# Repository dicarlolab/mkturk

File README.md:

# [mkturk](mkturk.com)
A purely web-based psychophysics tool for neuroscience and psychology

## Acknowledgement
We are happy to share the mkturk software and hardware and hope it helps with your project. Should this repository help in a substantitive way toward a publication, we would appreciate a brief acknowledgement: "Issa Lab for sharing their web based behavior system (mkturk)."

## Getting started
For getting the web app up and running, see https://mkturk.com/installation.html
Then see the [general guide](https://mkturk.com/features.html) & [detailed guide](https://paper.dropbox.com/doc/MkTurk-Guide--BF6Zcm6igbE2cwsKtibyddKOAg-Vpip4yINDsGnF3JwvBcJT)
[Full list of task parameter definitions](https://github.com/issalab/mkturk/tree/master/public/mkturk)

## Hosting the web app
Running mkturk is as simple as loading a web page since mkturk is purely a client-side piece of code. This requires a server capable of loading an html. Dropbox and Google Drive have stopped serving html, so other options have to be considered such as GitHub, GitLab, Google Firebase or Amazon S3.

### Local hosting of the web app
Even before publishing to the world wide web, mkturk can be run on a local host which is useful for development, debugging, and demo purposes.

### Configuring mkturk_installsettings.js
Compared to a regular app, a web app technically doesn't need to be installed in the traditional sense of the word. However, there are still some deployment-specific options to configure, and these are all found in mkturk_installsettings.js.

## Browser Compatibility
Although as a web app, mkturk should run on any browser on any device, in reality, we rely on Google Chrome which implements the latest APIs such as the WebUSB API. MkTurk will also run on Safari and Firefox browsers if not using an Arduino (which would require Chrome's WebUSB API).

## Setting up the touchscreen device
Depending on the device and which version of Android, you may have control over various settings and will want to adjust the Settings such as touch sensitivity, screen brightness, hiding home menus, disabling side or top swipe menus, disabling automatic dimming of screen, etc.

A very important feature to add is a way to keep the screen on so that it doesn't shut off in the middle of the task. Rather than use an app, we found that by enabling Developer Options, we unlock a feature to keep the screen on. On the latest Android, navigate to Settings -> System -> Developer Options, and enable "Stay awake - Screen will never sleep while charging." Alternatively, you can download an app such as [Keep Screen On](https://play.google.com/store/apps/details?id=eu.aboutall.android.tools.kepscreenon&hl=en). Unfortunately, besides Developer Mode or an app, there is no setting in native Android to prevent the screen from shutting off.

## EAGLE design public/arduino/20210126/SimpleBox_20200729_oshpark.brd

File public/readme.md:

# Parameters

## TASK
Automator: Boolean on/off

AutomatorFilePath: File path to params for the automator curriculum.

BackgroundColor2D: specify the background color in hex (eg, #FFFFFF for white or #000000 for black). Not required in param file. If not provided, defaults to gray screen background (#7F7F7F)

CheckRFID: Time in milliseconds over which at least one matching RFID read is required so that agent doesn't get kicked off of task. If there is a read within the last CheckRFID ms, task continues, otherwise agent is locked out at start of next trial. CheckRFID <= 0 turns off RFID checking.

ChoiceGridIndex: For a same-different task, need to specify two locations, one for same choice (circle) and one for different choice (square).

ChoiceScale (computed internally and stored in ENV.ChoiceScale instead of provided by user in TASK): Size of choice circle and square in units of sample image width

ChoiceSizeInches: Size of choice circle and square in physical inches on the screen

ChoiceTimeOut: Time in milliseconds that subject has to make a choice in AFC task before trial aborts and new sample is displayed. This timeout applies to test response screen in SR2 or M2S and to choice response screen in same-different

ConsecutiveHitsITI: Maximum time in milliseconds allowed to elapse from the previous trial for the current trial to count toward reward accumulation for a string of correct responses. For example, if ConsecutiveHitsITI=8000, then subject has 8 seconds to complete the next trial successfully and the consecutivehits counter will be incremented. Otherwise, the number of consecutivehits will get set to 0

CurrentAutomatorStage: index of current training stage of automator.

FixationDuration: How long subject has to hold fixation touch in milliseconds for a successful fixation to register.

FixationMove: FixationMove=0, fixation image is presented at fixationGridindex. FixationMove=N, N>0, fixation image is presented at a randomly selected grid point and the fixation position is redrawn every N milliseconds. FixationMove > 0 can be used to train subjects to touch different screen locations or to calibrate an eyetracker.
FixationScale: Size of fixation image in units of sample image width.

FixationScale (computed internally and stored in ENV.FixationScale instead of provided by user in TASK params): Size of the fixation dot or image (ie FixationUsesSample=1) in units of sample image width

FixationSizeInches: Size of fixation dot or image (ie FixationUsesSample=1) in physical inches on the screen

FixationTimeOut: Time in milliseconds that subject has to acquire fixation before fixation dot or image extinguishes. If fixation times out, then it is just re-displayed (flashes) and no reward or punishment is administered (ie, trial is aborted)

FixationUsesSample: FixationUsesSample=0, a fixation circle is shown for subject to touch; FixationUsesSample=1, sample image is shown as the fixation image. This allows implementation of a trianing strategy where the subject has to engage the sample image nfixations number of times before the choice screen.

GridScale (deprecated, replaced by GridSpacingInches): Determines intergridpoint spacing. Can think of this as the resolution of grid. gridscale=1 means intergridpoint spacing is equal to the width of the sample image. Finer grid resolutions (gridscale<1) can be used for more precise sample positioning.

GridSpacingInches: Determines intergridpoint spacing in physical inches on screen.

HideChoiceDistractors: HideChoiceDistractors=1, hides the same or different button so that subject sees only the correct one to touch. Still gets punished if touches blank area where the incorrect button would have been. This only applies to same-different choice screen. See HideTestDistractors for test response screen used in SR2 and M2S.

HideTestDistractors: HideTestDistractors=1, hides the distractor choices so that subject only sees matching choice. Still gets punished if touches blank area where the incorrect button would have been.

Homecage: Where task was performed. 0=lab 1=subject's home

ImageBagsSample: List of (list of) paths, where entries at the top level are directories / imagepaths for the sample images of one group; e.g. [['/bear_images', '/dog_images'], '/face_images'] is a {bear, dog} versus face task

ImageBagsTest: List of (list of) paths, where entries at the top level are directories / imagepaths for the test images of one group; e.g. [['/buttons/bear_icon.png, '/buttons/dog_icon.png'], ['/buttons/face_icon1.png, '/buttons/face_icon2.png']]

ImageRewardsList: List of paths containing user-specified reward per image. Images in the image_reward_list file need to be referenced by their complete path. ImageReward values: 0=no feedback (no reward or punish for that sample image) >0=user set reward for that sample image, overrides bonus reward behavior. These can be partial lists. For images where reward is manually specified, then default bonus reward behavior is used. No corresponding list is used for test (choice) images. Instead, specify reward for a whole class by listing reward for each image in that class in ImageRewardsList.

InterTrialInterval: How long to wait after reward/punish is delivered before starting next trial. Only a gray screen is shown for InterTrialInterval milliseconds, followed by the fixation dot.

KeepSampleON: KeepSampleON=0, sample is presented only for sampleON milliseconds for a delayed match-to-sample, KeepSampleON=1 sample remains on during choice screen. This implements a spatial match to sample.

KeepTestON: KeepTestON=0, test is presented only for testON milliseconds, KeepTestON=1 test remains on during choice screen. This only applies to same-different task when responses are indicated on additional choice screen following test screen.

Liquid: 1=water 2=water-condensed milk 3=marshmallow slurry (4/30mL)

NConsecutiveHitsforBonus: How many consecutive hits subject needs for the reward amount to increase.  If NConsecutiveHitsforBonus=4, then subject will get 2x reward for correct responses on 4 consecutive trials, 3x reward for correct responses on 8 consecutive trials, up to nrewardmax times of 1x reward. This is a way to make chance on a 2AFC task be virtually < 50% since reward is jointly distributed across trials rather than independently on the current trial.

NFixations: Number of times fixation dot needs to be pressed to advance to the match to sample phase of the task. nfixations=1 means the subject simply has to press the fixation dot once before the sample is presented. This mode allow parametric control over fixed ratio scheduling.

NGridPoints: Number of display grid points in either direction. Produces square grid. 3x3 is typical. Images (fixation,sample, & test) will appear centered on one of the grid points. Grid is serially zero indexed by rows then columns. ngridpoints can be made larger to allow for more response choices to be simultaneously displayed.

NRewardMax: Max number of rewards that can be given for a successful trial. This caps how much extra (bonus) reward subject can get for successful completion of consecutive trials. If nrewardmax=3, then subject can get up to 3x reward for completing 3*NConsecutiveHitsforBonus consecutive trials successfully, and then would get 3x reward after that until gets a trial wrong.

NStickyResponse: Number of times subject can choose the same location on the screen before force them out of it by placing the correct answer somewhere else (i.e. if they have response bias, then on the next trial, the correct choice is drawn somewhere away from that bias). Currently not implemented for same-different task or SR2

NTrialsPerBagBlock: if 0, randomly samples from all bags (default: interleaved match-t0-sample), if >0, samples N consecutive images from the same sample image bag. This is equivalent to blocking the session so that training is done in object blocks rather than interleaving all objects. After N trials are completed for bag i, proceeds to next bag i+1 according to bag sequence specified in ImageBagsSample. When all bags have been sampled NTrialsPerBagBlock times, starts back at bag 0.

ObjectGridIndex: Used for SR task. If this variable is set, then each object is tied to a particular location on the grid. ObjectGrid.length must equal objectlist.length for appropriate assignment of each object label to a grid location

Pump: 1=adafruit peristaltic 2=submersible centrifugal tcs 3=diaphragm pump tcs 4=piezoelectric 3mL takasago 5=newer diaphragm pumps tcs 6=piezoelectric 7mL takasago

PunishTimeOut: Time out in milliseconds for incorrect responses. Black square and incorrect sound may be presented for feedback during this time.

RewardPer1000Trials: Amount of liquid reward in mL for 1000 correct trials. For macaques, this is around 100mL for every 1000 correct trials.

RewardStage: RewardStage=0 rewards for successful fixtion and skips the choice phase of task. RewardStage=1 rewards for selecting the correct choice.

SampleGridIndex: Index on grid where sample image appears. SampleGridIndex=4 centers the image on a 3x3 grid, where ngridpoints=3

SamplingStrategy: Determines how sample images are drawn: uniform_with_replacement, uniform_without_replacement, sequential

SampleOFF: Duration in milliseconds that a gray screen is presented after the sample image before the response screen. This implements the delay in a DMS task. SampleOFF=0, leads to no delay

SampleON: Duration in milliseconds that sample image is presented

SampleScale (computed internally and stored in ENV.SampleScale instead of provided by user in TASK params): Size of sample image in units of sample image width. sampleScale=1 displays a npx x npx image on npx x npx screen pixels on the screen (i.e. no up or down sampling/resizing/filtering of the image)

SampleSizeInches: Size of sample image in physical inches on the screen. sampleSizeInches = 0.834444 displays a 256 x 256 image on 256 x 256 screen pixels on the google pixel c screen (i.e. no up or down sampling/resizing/filtering of the image)

Separated: 0=subject was paired with conspecific during task, 1=individual housed was separated from conspecific

Species: marmoset, macaque, or human

StaticFixationGridIndex: Index on the grid where the fixation image will appear. If FixationMove>0, then StaticFixationGridindex is ignored.

Tablet (deprecated, replaced by auto-detected ENV.DeviceName): nexus9, samsung10, pixelc

TestGridIndex: Index on grid where test images (choices) appear.

TestON: TestON > 0 indicates a Same-Different task so that last screen is a new choice screen with same (circle) and different (square) buttons. Test image extinguishes after TestON milliseconds, followed by TestOFF pause, followed by choice screen. If KeepTestON=1, then test image is on for TestON milliseconds and then remains on for choice screen

TestOFF: Choice screen appears TestOFF milliseconds after test image is extinguished. If TestOFF=0, then test screen does not extinguish (go to blank gray) until same-different choice screen appears. If KeepTestON=1, then test image reappears during the same-different choice screen.

TestScale (computed internally and stored in ENV.TestScale instead of provided by user in TASK params): Size of the test image in units of sample image width

TestSizeImages: Size of the test image in physical inches on the screen

Weight: Weight in kilograms

## ENV
AgentRFID: If CheckRFID>0, then fetches AgentRFID from database to check against incoming RFID reads to determine if correct agent is performing task. If tag doesn't match AgentRFID, task locks out and waits for a valid tag read

BatteryLDT: Stores any status update from the battery API, L=battery level in %  D=estimated time until battery discharges  T=Date.now()-StartDate timestamp of latest battery status update

CanvasRatio: Ratio of the logical canvas pixels to the physical screen pixels = BackingStoreRatio/DevicePixelRatio

ChoiceRadius: Radius (width) of same circle (different square) in pixels. This is not set by the user. Rather, user specifies ChoiceScale, and then ChoiceRadius stores the actual pixel-based size in the json data file.

ChoiceColor: Defaults to white circle (same) and square (different) buttons for same-different choice screen

ChoiceScale: Size of choice circle and square in units of sample image width

CurrentDate: date & time when task session was initiated

DataFileName: complete file path and name of datafile

DevicePixelRatio: In a typical retina display, there can be a devicePixelRatio of 2 so that each 1x1 logical pixel is rendered using 2x2 logical pixels. This upsampling requires interpolation and can lead to blurring over your image. However, this can be compensated by setting the CanvasRatio = BackingStoreRatio/DevicePixelRatio

DeviceBrand: eg Not available (for google devices) or Apple

DeviceBrowserName: eg Chrome or Safari

DeviceBrowserVerion: eg 78.0.3904.90 or 12.0

DeviceGPU: eg Adreno (TM) 640 or Apple A9 GPU

DeviceName: the name of the device used by mkturk to search firestore records eg Pixel 4 XL or iPhone 6s Plus

DeviceOSName: eg Android 10 or iOS 12.0.1

DeviceOSCodename: eg Android or iOS

DeviceOSVersion: eg 10 or 12.0.1

DeviceScreenWidth: full window (viewport) pixels

DeviceScreenHeight: full window (viewport) pixels

DeviceTouchscreen: 0 (not available) or 1 (available), indicates if touchscreen functionality available on device

DeviceType:desktop or mobile

Eye.BlinkGracePeriod: time in milliseconds that eye is allowed to be outside the fixation window without counting it as a fixation break. Any period longer than Eye.BlinkGracePeriod milliseconds outside the window is considered a fixation break.

Eye.CalibXTransform: Stores the parameters from the linear regression fit of eye tracker's x,y --> screen x (eg x_screen = a*x + b*y + c)

Eye.CalibYTransform: Stores the parameters from the linear regression fit of eye tracker's x,y --> screen y (eg y_screen = a*x + b*y + c)

Eye.CalibType: type of calibration ('default': based on screen size, 'linear': linear regression fit)

Eye.NCalibPointsTrain: Number of points for fitting the regression

Eye.NCalibPointsTest: Number of points for testing the regression (usually set to the same number of points used for training)

Eye.CalibTrainMSE: The train MSE for NCalibPointsTrain training points

Eye.CalibTestMSE: The test MSE for NCalibPointsTest testing points

FixationRadius: Radius of fixation image in pixels. This is not set by the user. Rather, user specifies FixationScale, and then FixationRadius stores the actual pixel-based size in the json data file.

FixationColor: color of fixation dot if image is not used

FixationScale: Size of the fixation dot or image (ie FixationUsesSample=1) in units of sample image width

ImageHeightPixels: The height of the sample image in pixels. The image height is used as the unit for the vertical dimension. SampleScale, FixationScale, TestScale, or GridScale = 1 means correspond to 1 unit in terms of the sample image

ImageWidthPixels: The width of the sample image in pixels. The image width is used as the unit for the horizontal dimension. SampleScale, FixationScale, TestScale, or GridScale = 1 means correspond to 1 unit in terms of the sample image

Ordered_Samplebag_Filenames: Names of the sample image bags. Each bag is treated as a separate label class

Ordered_Testbag_Filenames: Names of the test image bags. Each test image bag serves as the label images for each sample class

Ordered_SampleImageRewardList: Reward specification for each image: -1=default behavior 0=now reward/punish feedback >0=fixed reward for that image, value overrides default task bonus reward behavior

ParamFileDate: Date of revision on dropbox of the parameter file used for loading the task.

ParamFileName: Name of the parameter file used for loading the task

ParamFileRev: Dropbox revision # of the parameter file. The revision number is used to determine if a new version of the parameter file was found

PhysicalPPI: physical quantity, should equal ENV.DevicePixelRatio*ENV.ViewportPPI, physical device pixels per inch

RewardDuration: How long the reward is dispensed in milliseconds of time the pump is on. RewardDuration is derived by the user-specified RewardPer1000Trials in mL and the calibration curve for that pump type. 

SampleScale: Size of sample image in units of sample image width. sampleScale=1 displays a npx x npx image on npx x npx screen pixels on the screen (i.e. no up or down sampling/resizing/filtering of the image)

ScreenRatio: the standard device pixel ratio for that screen assuming no scaling (retrieved from firestore device record if available)

ScreenSizeInches: physical quantity, recorded physical size of screen (retrieved from firestore device record if available)

ScreenSizePixels: physical quantity, recorded # of pixels of screen (retrieved from firestore device record if available)

Subject: Name of subject, chosen from pulldown menu at beginning of task.

TestScale: Size of the test image in units of sample image width

UserAgent: info from window.navigator.UserAgent

ViewportPixels: derived quantity computed as ENV.ViewportPixels = ENV.ScreenPhysicalPixels/ENV.DevicePixelRatio where ScreenPhysicalPixels is the screen spec retrieved from firestore, and DevicePixelRatio is from the scaling being used by the user as detected during the browser session

ViewportPPI: derived quantity, equals ENV.ViewportPixels[0]/ENV.ScreenSizeInches[0], viewport pixels per inch (computed from first screen dimension)

XGridCenter: The location of all grid points in pixels. Follows from user-specified NGridPoints and GridScale (e.g. to create a 3x3 grid with adjacent non-overlapping images, set NGridPoints=3, GridScale=1 and XGridCenters will be spaced by ImageWidthPixels)

YGridCenter: The location of all grid points in pixels. Follows from user-specified NGridPoints and GridScale (e.g. to create a 3x3 grid with adjacent non-overlapping images, set NGridPoints=3, GridScale=1 and YGridCenters will be spaced by ImageHeightPixels)

## TRIAL
AllFixationXYT: records all fixation touches as opposed to most recent fixation touch in FixationXYT. If NFixations > 1, then AllFixationXYT will have multiple touch entries on a given trial. X,Y=horizontal,vertical position of fixation touch in pixels T=time of touch measured during Date.now()

AutomatorStage: Stage number if Automator=1

CorrectItem: Index of the correct item on each trial

FixationGridIndex: Fixation grid location on each trial.

FixationTouchEvent: The type of touch event that was registered for that trial (e.g. touchheld or touchbroke if there was a required FixationDuration>0 period)

FixationXYT: records most recent fixation touch on each trial. X,Y=horizontal,vertical position of fixation touch in pixels T=time of touch measured using Date.now()

NReward: The number of rewards given at the end of each trial; usually 1x reward unless subject got many trials in a row correct in which case may get bonus reward according to nconsecutivehitsforbonus.

NRFID: total # of RFID tag reads

NWeights: total # of weight reads

Response: Index of the chosen item on each trial. For M2S and SR2, response is measured for touches on the test screen. For same-different task, this is collected at the choice screen.

ResponseTouchEvent: The type of touch event that was registered for that trial (e.g. touchheld, touchbroken, TimeOut)

ResponseXYT: records the coordinates and time of touching the choice item. X,Y=horizontal,vertical position of response touch in pixels T=time of touch measured using Date.now()

RFIDTag: tag read 

RFIDTime: time in milliseconds that tag was read

RFIDTrial: trial# during which tag was read

Sample: Index of sample displayed on each trial. Index into list of imagebags for that session

StartTime: Time recorded when the most recent fixation dot was shown for that trial.

Test: Indices of test choices displayed on each trial where N indices are stored for an N-AFC task. Index into list of test imagebags for that session

Weight: weight in grams

WeightTime: time in milliseconds of weight reading

WeightTrial: trial # during which tag was read

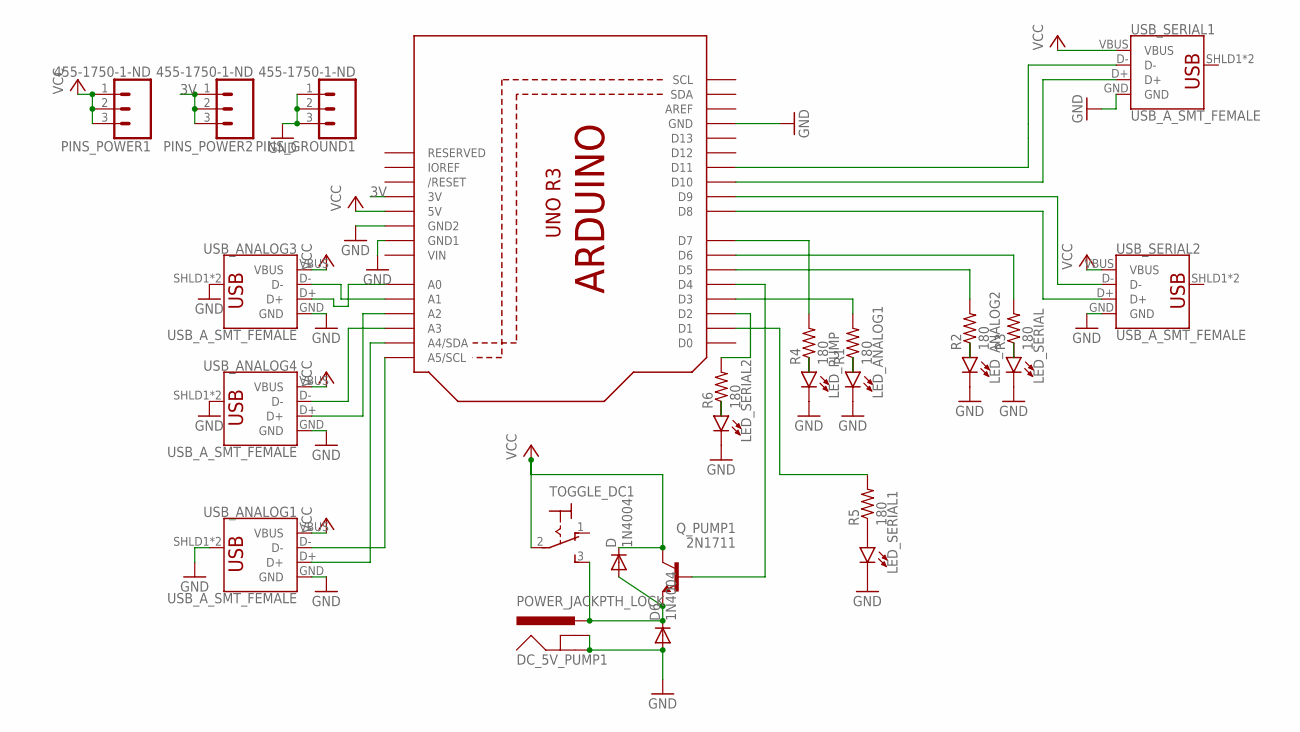
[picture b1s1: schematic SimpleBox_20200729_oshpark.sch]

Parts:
D, D6: 1N4004; DO41-10
DC_5V_PUMP1: POWER_JACKPTH_LOCK; POWER_JACK_PTH_LOCK
LED_ANALOG1, LED_ANALOG2: LED5MM; LED_5MM
LED_PUMP: LED5MM; LED_5MM
LED_SERIAL, LED_SERIAL1, LED_SERIAL2: LED5MM; LED_5MM
PINS_GROUND1: 455-1750-1-ND; 1X03
PINS_POWER1, PINS_POWER2: 455-1750-1-ND; 1X03
Q_PUMP1: 2N1711; TO39
R1, R2, R3, R4, R5, R6: 180; 0204/7
TOGGLE_DC1: M9040P
U1: ARDUINOR3-BPLACE
USB_ANALOG1, USB_ANALOG3, USB_ANALOG4: USB_A_SMT_FEMALE; USB-A-S-SILK-FEMALE
USB_SERIAL1, USB_SERIAL2: USB_A_SMT_FEMALE; USB-A-S-SILK-FEMALE

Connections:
3V: PINS_POWER2.1, PINS_POWER2.2, PINS_POWER2.3, U1.3V
GND: D6.A, DC_5V_PUMP1.GND, DC_5V_PUMP1.GNDBREAK, LED_ANALOG1.K (C), LED_ANALOG2.K (C), LED_PUMP.K (C), LED_SERIAL.K (C), LED_SERIAL1.K (C), LED_SERIAL2.K (C), PINS_GROUND1.1, PINS_GROUND1.2, PINS_GROUND1.3, U1.GND, U1.GND1, U1.GND2, USB_ANALOG1.GND, USB_ANALOG1.SHLD1 (SHIELD), USB_ANALOG1.SHLD2 (SHIELD), USB_ANALOG3.GND, USB_ANALOG3.SHLD1 (SHIELD), USB_ANALOG3.SHLD2 (SHIELD), USB_ANALOG4.GND, USB_ANALOG4.SHLD1 (SHIELD), USB_ANALOG4.SHLD2 (SHIELD), USB_SERIAL1.GND, USB_SERIAL2.GND
unnamed: LED_ANALOG1.A, R1.1
unnamed: LED_ANALOG2.A, R2.1
unnamed: LED_SERIAL.A, R3.1
unnamed: LED_PUMP.A, R4.1
unnamed: U1.A3, USB_ANALOG4.D-
unnamed: U1.A2, USB_ANALOG4.D+
unnamed: U1.A1, USB_ANALOG3.D-
unnamed: U1.A0, USB_ANALOG3.D+
unnamed: U1.D8, USB_SERIAL2.D+
unnamed: U1.D9, USB_SERIAL2.D-
unnamed: Q_PUMP1.2 (B), U1.D4
unnamed: U1.D11, USB_SERIAL1.D-
unnamed: U1.D10, USB_SERIAL1.D+
unnamed: LED_SERIAL1.A, R5.1
unnamed: R4.2, U1.D7
unnamed: LED_SERIAL2.A, R6.1
unnamed: R5.2, U1.D1
unnamed: U1.A5 (A5/SCL), USB_ANALOG1.D-
unnamed: R3.2, U1.D6
unnamed: R6.2, U1.D2
unnamed: R1.2, U1.D3
unnamed: U1.A4 (A4/SDA), USB_ANALOG1.D+
unnamed: R2.2, U1.D5
unnamed: D.A, D6.C, DC_5V_PUMP1.PWR, Q_PUMP1.1 (E), TOGGLE_DC1.3 (S)
VCC: D.C, PINS_POWER1.1, PINS_POWER1.2, PINS_POWER1.3, Q_PUMP1.3 (C), TOGGLE_DC1.2, U1.5V, USB_ANALOG1.VBUS, USB_ANALOG3.VBUS, USB_ANALOG4.VBUS, USB_SERIAL1.VBUS, USB_SERIAL2.VBUS
VIN: U1.VIN

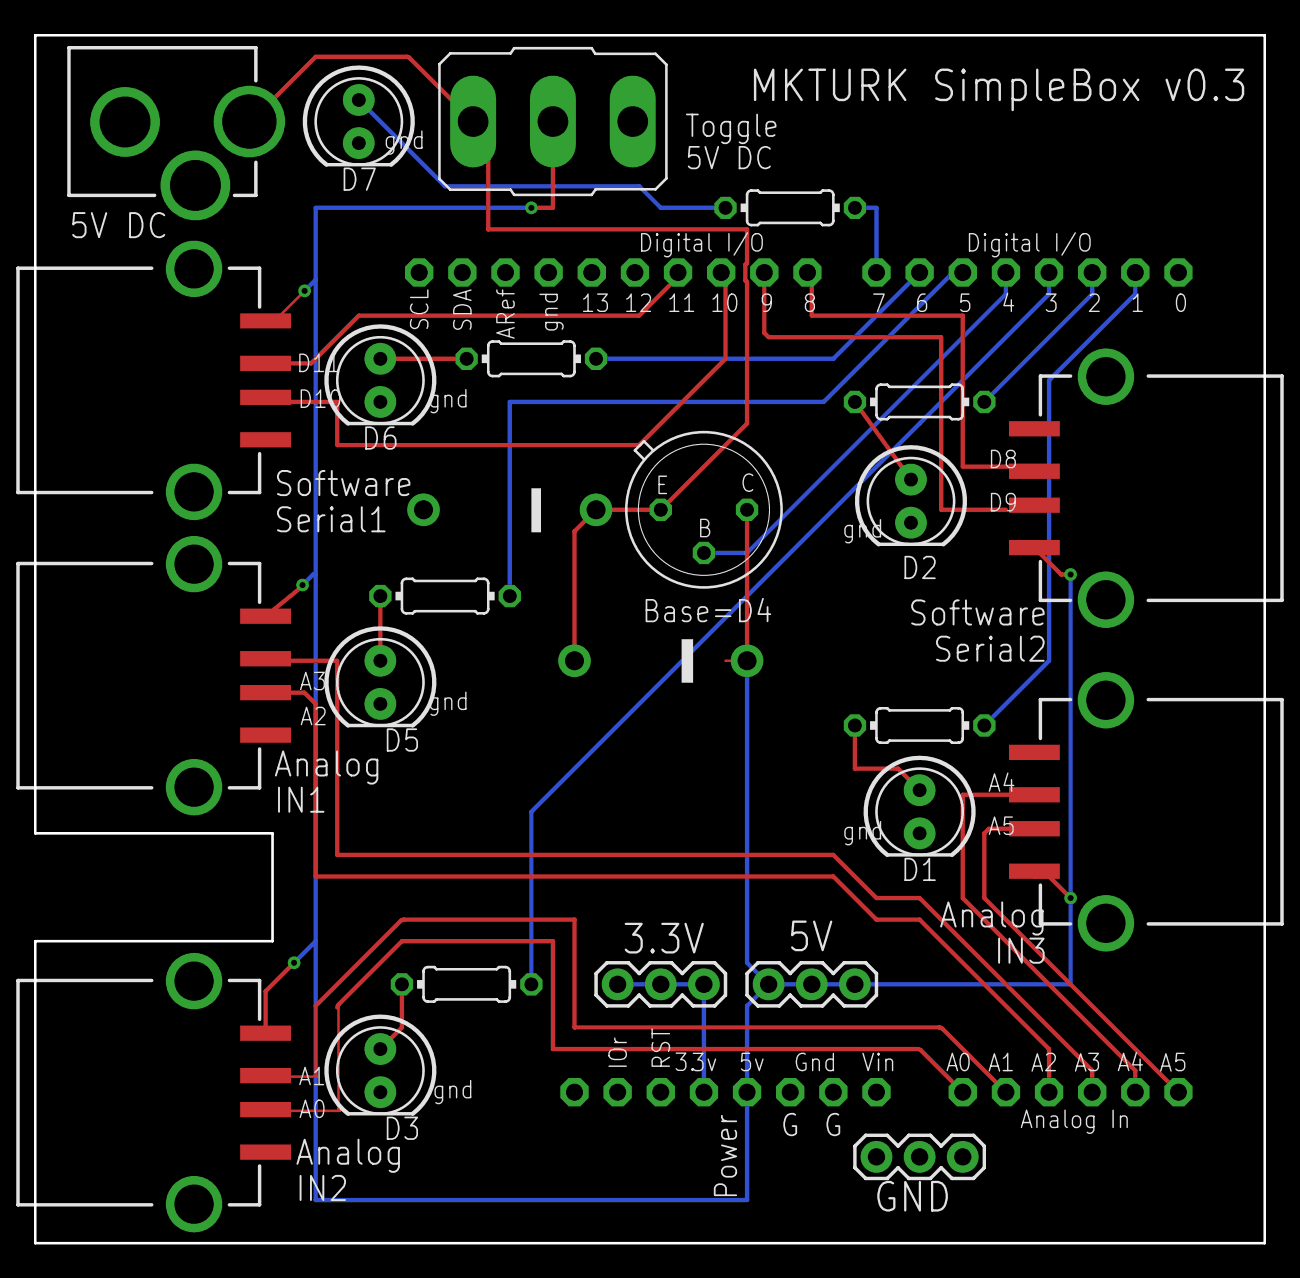
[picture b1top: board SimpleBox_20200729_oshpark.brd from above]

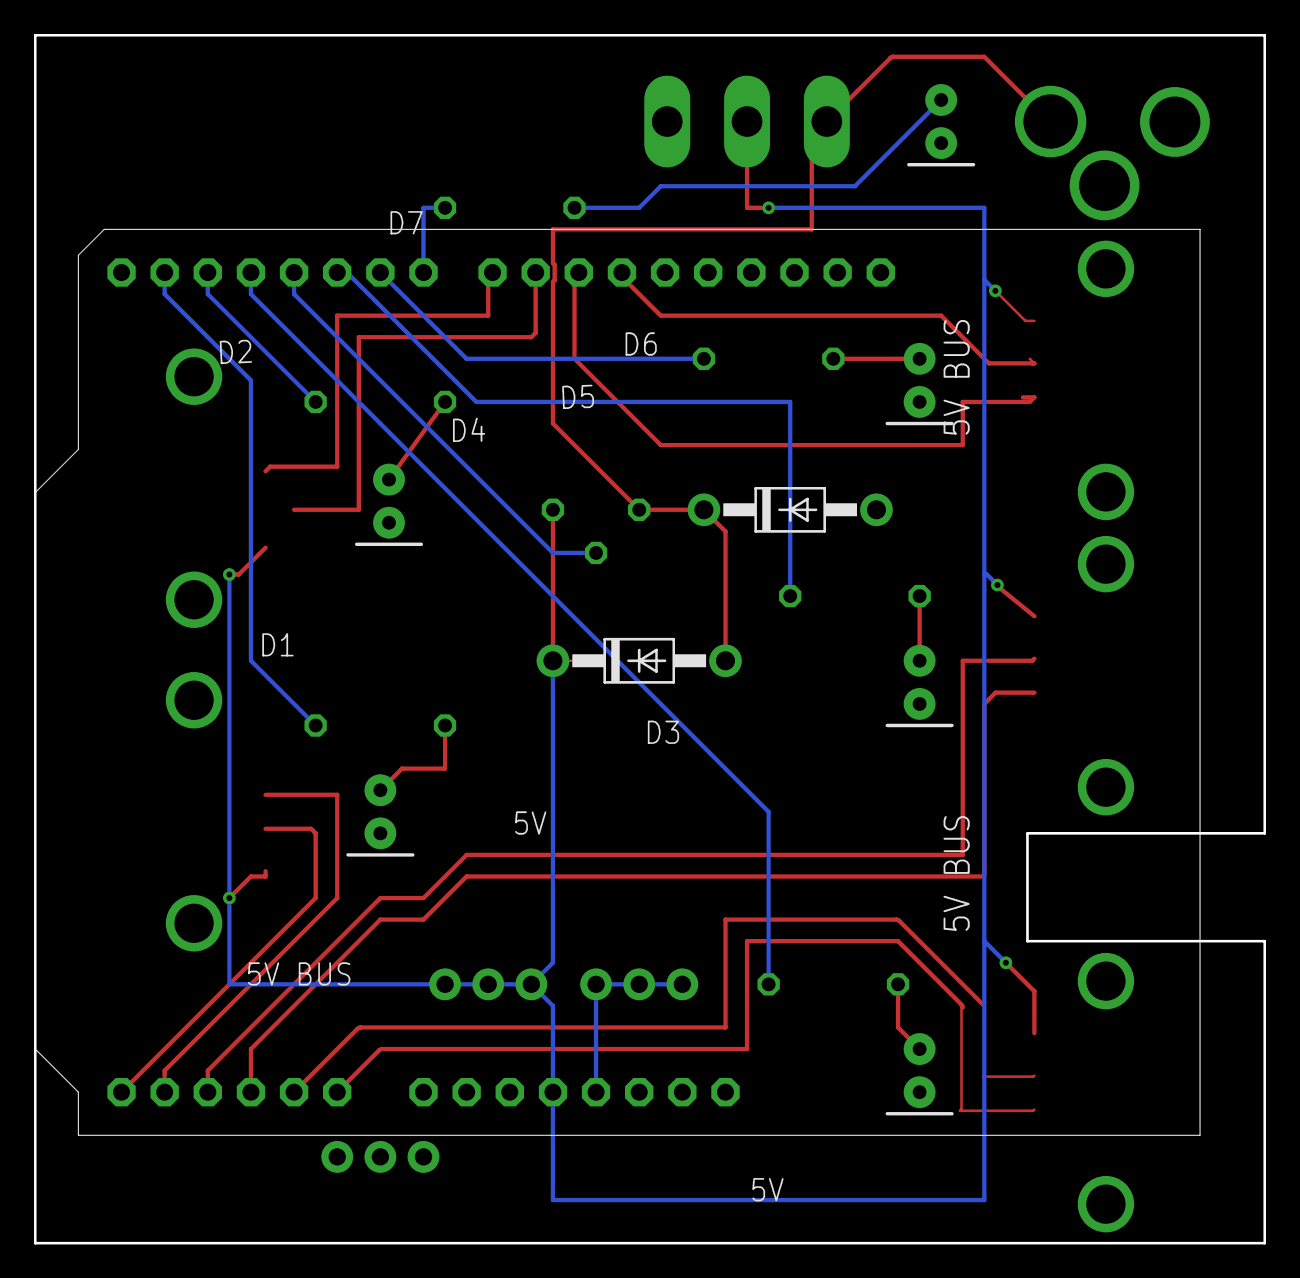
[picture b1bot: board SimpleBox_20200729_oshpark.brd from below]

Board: 2 copper layers, 72.4 x 71.1 mm, 26 parts (2 on the bottom side), 27 nets.

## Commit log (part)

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2020-04-16 add icon to mkturk landing page
2020-04-17 added signin modal
2020-04-18 Fix 3d canvas bug on task parameter changes
    "The problem is that when the parameter changes, canvasvisiblewebgl’s size defaults to the original canvas size, not taking into account ENV.THREEJSrenderratio which is currently 4. If you check the 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
    Solved by putting setupCanvas & initThreeJS at same location so that webgl canvas size is not reset by setupCanvas unless followed by a setRenderRatio in initThreeJS (ie, a completely new scene is be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
2020-04-23 writing cloud function isLabMember
2020-04-24 moved mkfiles_src/ into ~/src/mkfiles
2020-04-27 copy master
2020-04-29 Mkfiles: added duplicate functionality for scenes & rename functionality for textfiles in cloud storage
2020-04-30 fixed bug related to buttonBox in editor div
2020-05-03 MAJOR: RSVP (part 1 of n)
    Add RSVP task. This is a working prototype where during sample screen can display a string of TASK.NRSVP sample images drawn according to TASK.SamplingStrategy. Only implemented for threeJS/trialqueu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
    RSVP uses sample screen because still need a fixation screen for holding fixation in center prior to display of sample image sequence
    RSVP will forgo Test/Choice screens and reward based on fixation duration (not implemented yet in this protoype).
    To accommodate a sequence of sample images, code expands sample sequence into frames composed of clips (each sample image or movie) and frames within a clip (eg, a
2020-05-04 new website template
2020-05-12 THREEJS animation: 2D background,visibility, opacity
    additional bug fixes for updating Test Images
2020-05-30 MAJOR: Streamline mkturk 3D scene & 2D image display
    Under-the-hood changes in how mkturk displays movies to be more compatible with universal frame-by-frame sequence display. Merges Sample & Test behavior so that both can be movies (only Sample can be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
    index.html: (1) No longer get image width and compute FixationScale, SampleScale, TestScale, and ChoiceScale. (2) Merge Sample & Test behavior so that both can be movies. Expand out frame sequence wi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
2020-06-02 THREEJS morphAnimation
2020-06-04 THREEJS morphing Animation
2020-06-08 rewriting fireplace as proof of concept for webworkers & offscreencanvas
2020-06-10 sampling from gaussian dist
2020-06-12 Fixes for saving out of Sample & Test screens to images
    Handles image & movie and RSVP sequences
    Expands out static image frame-by-frame and lets displayTrial handle when to update (or not) on the backend.
2020-06-15 remove trialqueue
2020-06-24 scene generator
2020-06-24 mkTurk3d_tutorial images
2020-06-25 minor change for animating transparency
2020-06-26 mkcolony revamp
2020-07-11 Save display times to BigQuery, Vary Sample location with moving Fixation, fix trial initiation with eyetracking
    - Added saving to BigQuery of desired and actual frame display times. Each row contains a column for actual and a column for desired which stores an array of variable length depending on movie length.
    - When fixation moves (FixationGridIndex<0), now sample appears behind it if SampleGridIndex <0. Removed variables StaticFixationGridIndex & FixationMove.
    -There was an issue with eyetracking initiating an RSVP trial after the first one. Needed to manually reset various FLAGS since an RSVP trial skips the fixation acquisition step.
    - Fixed threejs rendering issue with face on chan
2020-07-20 problem with clean copy
2020-07-21 mkcolony done. need to finish interface with mkscale
2020-07-29 done with mkcolony rfid integration
2020-08-05 makeActive json
2020-08-18 smart text
2020-08-24 logbook editor set
2020-09-01 mkcolony2
2020-09-03 change json files to new format
2020-09-04 done
2020-09-18 logsheet viewer on mkcolony done
2020-09-23 prepare to bring master
2020-09-25 tweaks to screen saving & filters, cleaned up !offscreencanvasavailable logic
2020-10-01 Add fixation dot, add reaction time histogram to liveplot
    Add fixtion dot overlay. New parameter FixationDotSizeInches.
    Add fixation window. New parameter FixationWindowSizeInches (SampleFixationSizeInches is deprecated).
    If FixationWindowSizeInches>0, this is used for fixation & sample screen bounding boxes overriding the fixation or sample display element's bounding box.
    Both fixation dot & fixation window are applied to the fixation and sample screens (not to test or choice screens) and are intended for fixation tasks such as RSVP.
    Cleaned up the way mkturk saves timestamps in a fixation task and how it specifies Response & Correctitem so that it's easier for liveplot & fireplace to g
2020-10-02 10/2 progress
2020-10-07 done with gif
2020-10-08 feature change
2020-10-15 updated movie gifs
2020-10-16 merged w/ master
2020-10-23 liveplot w/ rtdb init
2020-10-26 trying to not create sourcemap for css files
2020-10-27 website finalized
2020-10-27 liveplot cont
2020-10-29 building a types interface for Liveplot to reduce code logic in charts.ts
2020-10-30 starting loadChoiceData
2020-11-03 realtime mirroring works
2020-11-04 coordinate fix
2020-11-06 pull rqst rdy
2020-11-08 transaction bug fix
2020-11-11 mkmodels
2020-11-20 fix issue with mouse tracking
    Mouse tracking was cutting off at top of screen because of overlying but invisible text elements
2020-12-10 dealt with input pipeline lag:
2020-12-16 standardization:
2020-12-21 work
2020-12-22 model in mkturk
2020-12-23 save images options
2020-12-23 remove console
2021-01-06 processMturkUser cloud function now needs to add the custom wid claim
2021-01-11 finished processMturkUser. writing verifyMturkSubmission
2021-01-14 mkturk index.js refactor + mturk integration
2021-01-19 almost done
2021-01-22 migration
2021-01-26 better manage how automator updates files
    add folder for ardunio code
    only have automator save after all parameters are set
2021-01-28 survey form
2021-02-06 MAJOR: add photodiode square (prototype code)
    Implemented square at bottom right of screen that goes from white to black to trigger the photodiode.
    Updated the arduino code to handle photodiode events and unified how events are sent back to mkturk for benchmarking (sample command, pump command, and photodiode).
    Sample command, pump command, and photdiode times are sent back from the arduino merged into one stream for keeping track of hardware times.
    Note, this is prototype code. Will add hardware times to text updates in practice mode, a cloud function to send to bigquery, and eventually add a route for liveplot2 realtime streaming
2021-02-10 automator fix
2021-02-11 Revert "for debugging the photodiode times"
    This reverts commit 57decf044fb22f7ba50bfd75ae30c794f48776bc.
2021-02-15 liveplot realtime for nrsvp init
2021-02-19 boundingBoxesRtdb
2021-02-22 update packages for mkfiles
2021-02-24 svm classifier
2021-02-28 Minor updates to firestore & readme
    Firestore refresh countdown timer
    ViewportPPI computed using largest screen dimension
    Updated home readme to link to mkturk.com and parameter readme
    Updated parameter readme, particularly trialevents and timeevents
    AllFixationXYT removed completely
2021-03-03 create custom bounding boxes for image/object capture
2021-03-05 MkModels now works with SameDifferent. Need to create more sceneparams for robust testing. Need to change sizing to avoid normalization during downsampling to 224
2021-03-05 writing balancing code
2021-03-09 minor changes: set PunishTimeOut=0 for models; TRAINING counter updated
2021-03-10 outputNode for tfjs
2021-03-12 added mkscenes.ts
2021-03-12 adding helper functions for mkscenes
2021-03-17 clean and replace empty cell in a sparse array in mkturk_firestore.js
2021-03-17 changes to functions
2021-03-18 make samplecommand contingent on arduino available
2021-03-18 Remove arduino webusb data saving
2021-03-19 fix overlapping line drawings and different colors for each series
2021-03-22 Sample Command trigger only issued during savedata phase
2021-03-23 click/hover
2021-03-30 Remove await for SampleCommand
    Awaiting SampleCommand trigger led to long and variable delays of seconds between mkturk and the camera. Camera would go before mkturk would do image display. Removing the await led to millisecond le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
2021-03-31 mkfiles scene gen, mkturk website complete
2021-04-02 screenfunction render2d fix init
2021-05-25 cubeBackground beta
    - added camera position animation
    - 2d background is rendered on a cube for immersive room experience
    testing for rendering speed on phones
2021-07-08 MAJOR: 3d background, crop functionality
    - background images are rendered as a cube in THREEJS
    - user can crop parts of images by assigning crop value in a scenefile
2021-07-15 print times
2021-07-20 create dedicated development folder
    - return mkturk to master mkturk
    - create mkturky folder for development
2021-07-22 health plot init
2021-07-23 change location of logging eyetrackersampleinterval
2021-07-27 minor updates
    - fixes trigonometry equations
2021-07-27 add ENV.WebAppUrl to MkTurk
2021-07-27 fixing spelling mistakes in liveplot2
2021-07-29 lp3 cont
2021-08-03 changed liveplot2 code to include tdisplay_first, changed mkturk_usb.js s.t. samplecommand receiving code is outside of the else statement
2021-08-04 Update mkturk_firebasestorage.js
    - use getFileList instead of getFileListRecursive
    - use textureLoad instead of imageload
2021-08-04 remove original mkparams
2021-08-04 duplicate current mkturk to mkturk-lab
2021-08-05 Clean-up after major updates
    Removed remnants of offscreen canvas code. Removed console logging that was used in debugging. Updated readme to describe new TASK and TRIALEVENTS variables. Updated manifest.json so that reload woul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
2021-08-12 continue orthographic
2021-08-17 adding bqInsertTouchData to functions/
2021-08-18 redeploy eye and display time functions and add touch function for bigquery
2021-08-24 debugging eyetrackersampleinterval issue
2021-08-25 changed BigQuery saving logic and added Orthographic camera to mkturk/
2021-08-25 changed index from i to j in trialqueuescene
2021-08-26 change liveplot2 to plot anything available for health stats
2021-09-08 figured out srcX and srcY
2021-09-15 my code ready before merging younah's code
2021-09-20 mkfiles does not display automator variables correctly
2021-09-23 firebase v9
2021-09-29 trying to fix orthographic for mkturk-lab
2021-10-04 orthographic camera fix and mkturk_threejs refactor complete
2021-10-07 reordering done. mkfiles react init
2021-10-08 dev install
2021-10-12 hooks and redux
2021-10-14 add thunk
2021-10-19 incorporating data grid
2021-10-19 enable list view by default
2021-10-21 automator update
2021-10-23 older eyetracker calib code saved for testing
2021-10-29 gui to control objects in mkfiles & younah's edits to mkturk-lab
2021-11-01 adding cubemap feature in mkfiles
2021-11-02 mkturk_screenfunctions.js change: add behavior when taskcreen is Blank in displayTrial
2021-11-05 change
2021-11-10 change to mturkcode
2021-11-11 additional changes
2021-11-15 queryDevice function in mkturk-lab is ready; mkfiles accomodates reading mturk files; liveplot update
2021-12-07 fix savescreenshot
    - only saves canvasvisible, not webgl canvas
    - adds FLAGS.movieper for movies where the camera is moving
2021-12-10 new user management system

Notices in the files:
parts and their libraries:
SparkFun-Connectors: Licensing: Creative Commons ShareAlike 4.0 International - https://creativecommons.org/licenses/by-sa/4.0
